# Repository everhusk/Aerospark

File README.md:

Rockoon Project
====================

[Click here to read the full paper](https://github.com/everhusk/Aerospark/blob/master/Design%20%26%20Analysis%20Of%20A%20Lunar%20Mission%20Launched%20From%20A%20HAB.pdf)

This project was developed as an open source experiment of the “rockoon” concept.  The basic idea is to launch a rocket from a high altitude balloon at, or near, it’s burst altitude.  The purpose of this experiment is to demonstrate alternative technology to reach space.

A full overview of the technology and a detailed study of the concept is available in the PDF document titled “Design and Analysis of a Lunar Mission Launched From a High Altitude Balloon”.

The payload contains a Raspberry Pi with the Aerospark shield, and a RockBLOCK unit which plugs directly into the Pi’s USB port.  Once powered, load the code to the Pi, edit the desired altitude, and make sure you have credits on your RockBLOCK.  Once the altitude is reached, the ignition relay will close the ignition circuit and fire the rocket.  Tracking is provided by the Iridium satellite network which is published by RockBLOCK through HTTP requests to the Aerospark website.

Iridium SBD
================

This folder contains a few python and node.js scripts for communicating with a RockBLOCK Iridum unit.

In the python folder you will find a code to allow you to send simple commands to the RockBLOCK directly from the terminal window by running:
```
// python hello_iridium.py -d /dev/ttyUSB0
```
For a detailed list of all of the commands visit: http://tabs2.gerg.tamu.edu/~norman/659/9602DevelopersGuide_RevisionBEAM.pdf

To initiate a SBD session and transmit "Hello World" to the iridium network:
```
// python run_iridium.py -d /dev/ttyUSB0
```

The node.js folder was obtained from the RockBLOCK website, and can also be used for communicated with the RockBLOCK.

Flight Computer
============

The master flight computer code for the HAB/Rockoon launch is available in this code.

PCB
===

The Aerospark Printed Circuit Board is also available.  Eagle files are included in this folder.

Licence
======

[MIT Licence](http://opensource.org/licenses/MIT)

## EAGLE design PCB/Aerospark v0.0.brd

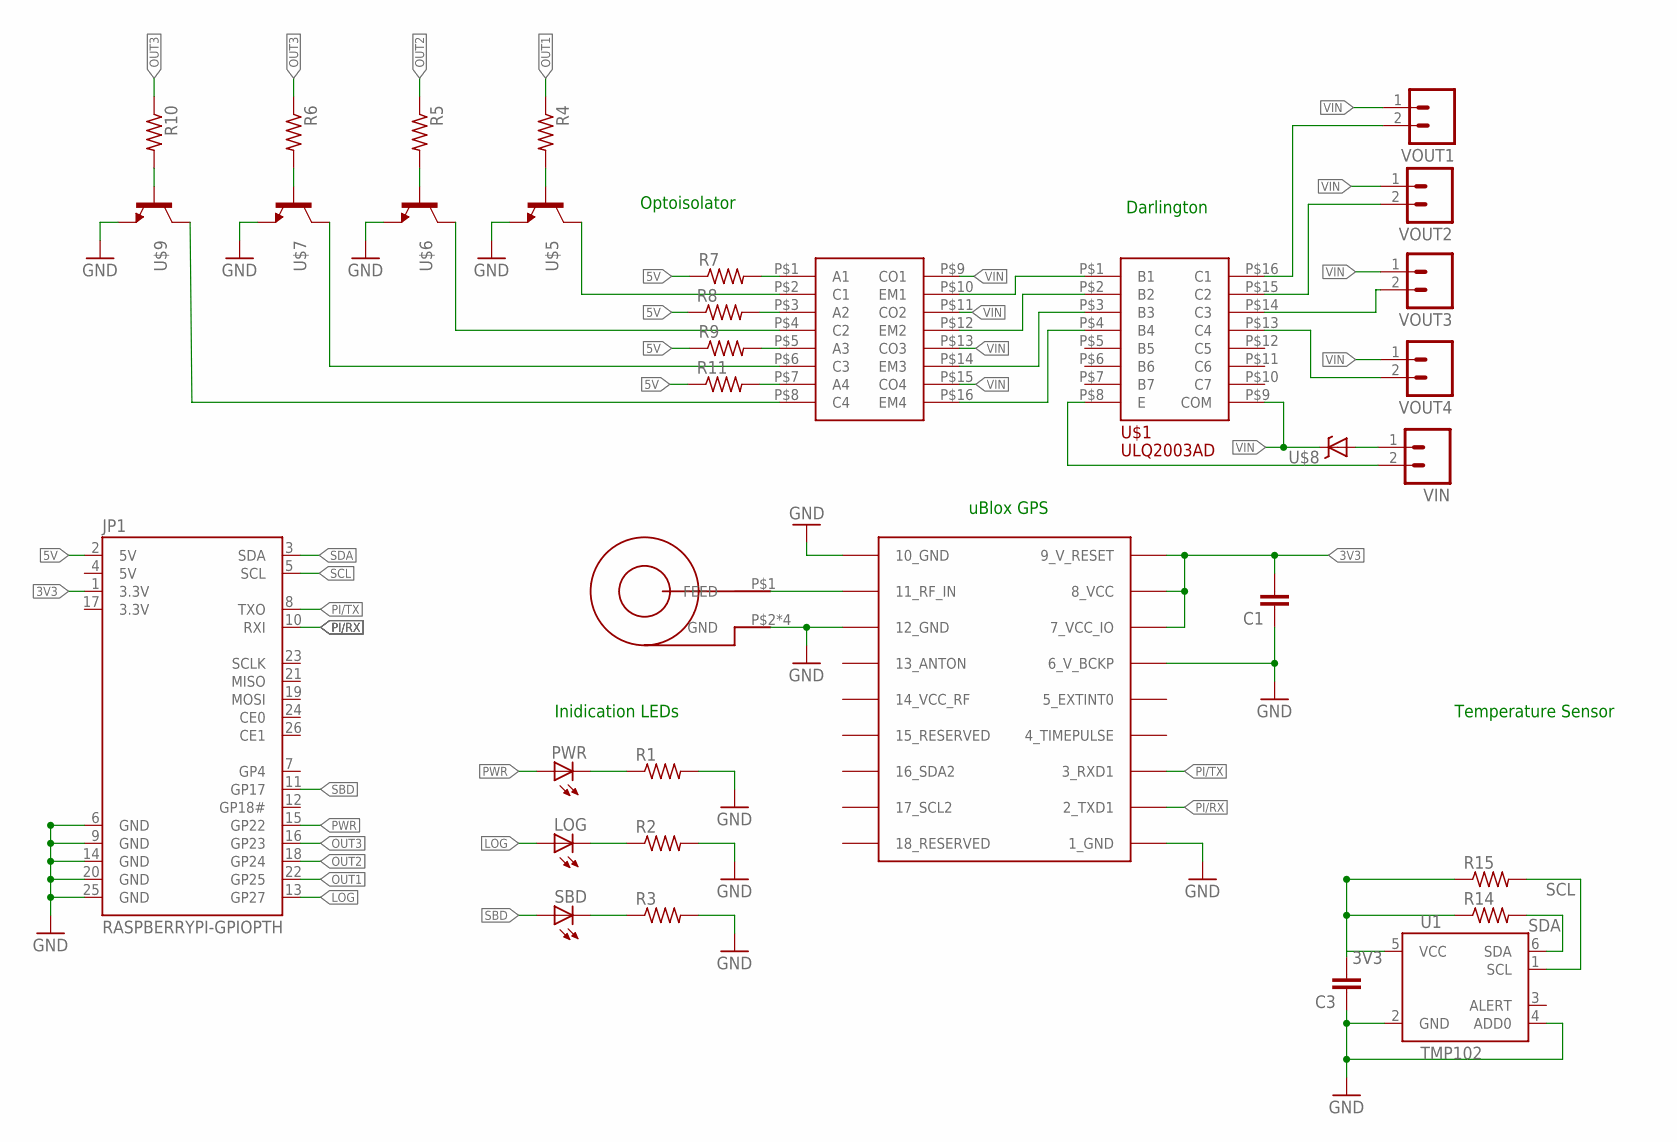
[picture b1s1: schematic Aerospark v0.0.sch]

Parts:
C1, C3: CAP0805; 0805
JP1: RASPBERRYPI-GPIOPTH; 2X13-SHROUDED
LOG: LEDCHIPLED_0805; CHIPLED_0805
PWR: LEDCHIPLED_0805; CHIPLED_0805
R1, R2, R3: R-US_R0805; R0805; MPN CMD17-21VGD/TR8
R4, R5, R6, R7, R8, R9, R10, R11, R14, R15: R-US_R0805; R0805
SBD: LEDCHIPLED_0805; CHIPLED_0805
U1: TMP102; SOT563
U$1: ULQ2003A; SOIC
U$2: UBLOX_MAX
U$3: JDGA-REMQV-ANTENNA; JDGA-RIGID_COMBO_PAD
U$5, U$6, U$7, U$9: MMBT3904FSCT-ND; SOT-23
U$8: VISHAY_SCHOTTKY; DO-220AA
U$11: K847PH; DIP16
VIN: M023.5MM_LOCK; SCREWTERMINAL-3.5MM-2_LOCK
VOUT1, VOUT2, VOUT3, VOUT4: M023.5MM_LOCK; SCREWTERMINAL-3.5MM-2_LOCK

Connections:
3.3V: JP1.17 (3.3V)
3V3: C1.2, C3.2, JP1.1 (3.3V), R14.1, R15.1, U1.5 (VCC), U$2.7_VCC_IO, U$2.8_VCC, U$2.9_V_RESET
5V: JP1.2 (5V), JP1.4 (5V), R7.1, R8.1, R9.1, R11.1
GND: C1.1, C3.1, JP1.6 (GND), JP1.9 (GND), JP1.14 (GND), JP1.20 (GND), JP1.25 (GND), R1.2, R2.2, R3.2, U1.2 (GND), U1.4 (ADD0), U$2.1_GND, U$2.6_V_BCKP, U$2.10_GND, U$2.12_GND, U$3.P$2 (GND), U$3.P$3 (GND), U$3.P$4 (GND), U$3.P$5 (GND), U$5.3 (E), U$6.3 (E), U$7.3 (E), U$9.3 (E)
LOG: JP1.13 (GP27), LOG.A
unnamed: U$2.11_RF_IN, U$3.P$1 (FEED)
unnamed: R7.2, U$11.P$1 (A1)
unnamed: PWR.C, R1.1
unnamed: LOG.C, R2.1
unnamed: R3.1, SBD.C
unnamed: R8.2, U$11.P$3 (A2)
unnamed: R9.2, U$11.P$5 (A3)
unnamed: U$1.P$16 (C1), VOUT1.2
unnamed: U$5.2 (C), U$11.P$2 (C1)
unnamed: U$1.P$1 (B1), U$11.P$10 (EM1)
unnamed: U$6.2 (C), U$11.P$4 (C2)
unnamed: U$7.2 (C), U$11.P$6 (C3)
unnamed: U$1.P$8 (E), VIN.2
unnamed: R4.2, U$5.1 (B)
unnamed: R5.2, U$6.1 (B)
unnamed: R6.2, U$7.1 (B)
unnamed: U$8.ANODE (A), VIN.1
unnamed: U$1.P$15 (C2), VOUT2.2
unnamed: U$1.P$14 (C3), VOUT3.2
unnamed: U$1.P$13 (C4), VOUT4.2
unnamed: U$1.P$3 (B3), U$11.P$14 (EM3)
unnamed: U$1.P$2 (B2), U$11.P$12 (EM2)
unnamed: R10.2, U$9.1 (B)
unnamed: U$9.2 (C), U$11.P$8 (C4)
unnamed: R11.2, U$11.P$7 (A4)
unnamed: U$1.P$4 (B4), U$11.P$16 (EM4)
OUT1: JP1.22 (GP25), R4.1
OUT2: JP1.18 (GP24), R5.1
OUT3: JP1.16 (GP23), R6.1, R10.1
PI/RX: JP1.10 (RXI), U$2.2_TXD1
PI/TX: JP1.8 (TXO), U$2.3_RXD1
PWR: JP1.15 (GP22), PWR.A
SBD: JP1.11 (GP17), SBD.A
SCL: JP1.5 (SCL), R15.2, U1.1 (SCL)
SDA: JP1.3 (SDA), R14.2, U1.6 (SDA)
VIN: U$1.P$9 (COM), U$8.CATHODE (C), U$11.P$9 (CO1), U$11.P$11 (CO2), U$11.P$13 (CO3), U$11.P$15 (CO4), VOUT1.1, VOUT2.1, VOUT3.1, VOUT4.1

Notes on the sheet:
Inidication LEDs
uBlox GPS
Temperature Sensor
Optoisolator
Darlington

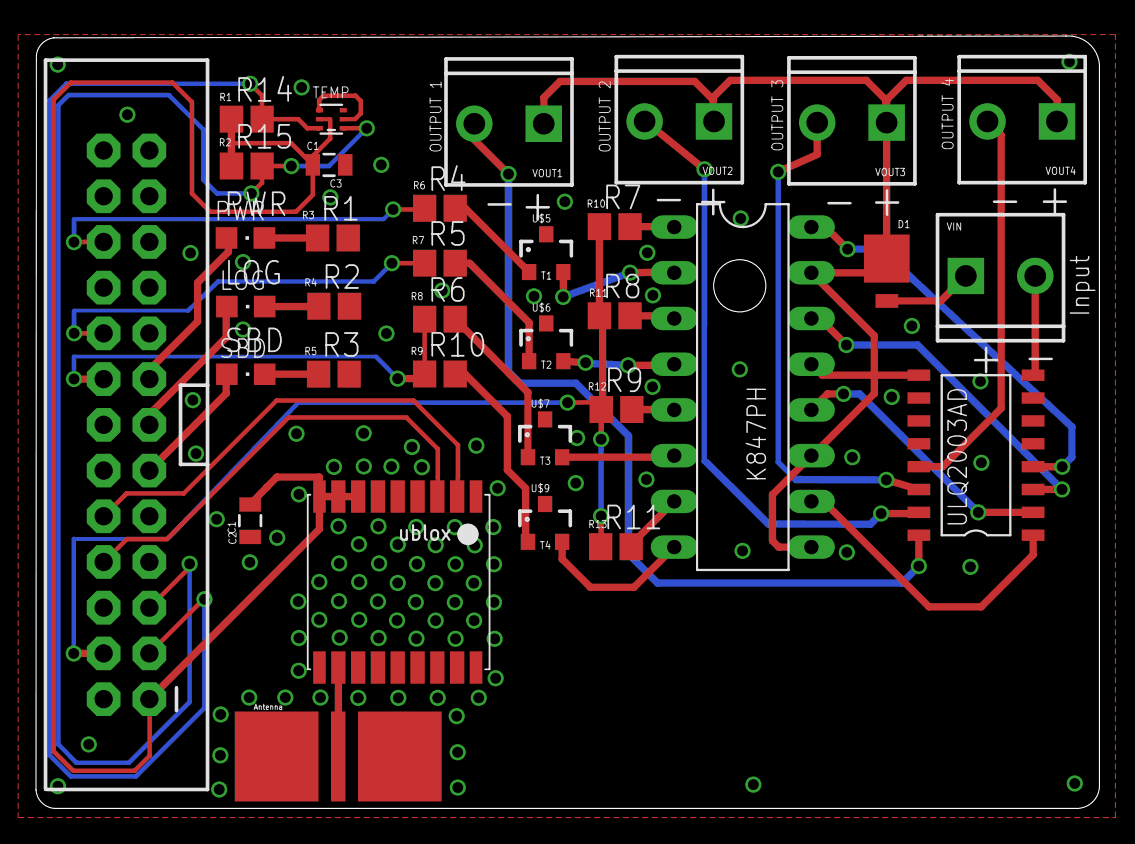
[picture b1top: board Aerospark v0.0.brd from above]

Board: 2 copper layers, 59.1 x 42.9 mm, 34 parts (0 on the bottom side), 40 nets.

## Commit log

2014-07-11 PCB Version 1.0 - Final
2014-07-11 Updated PCB to v1.1
2014-07-14 Updated PCB to optoisolator & darlington drivers
2014-07-14 Updated PCB and added mounting hole
2014-07-15 Shipped PCB v0.0

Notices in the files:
parts and their libraries:
SparkFun-Boards: Licensing: Creative Commons ShareAlike 4.0 International - https://creativecommons.org/licenses/by-sa/4.0
